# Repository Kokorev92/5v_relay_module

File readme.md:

# Relay module for arduino

A simple relay module for Arduino.

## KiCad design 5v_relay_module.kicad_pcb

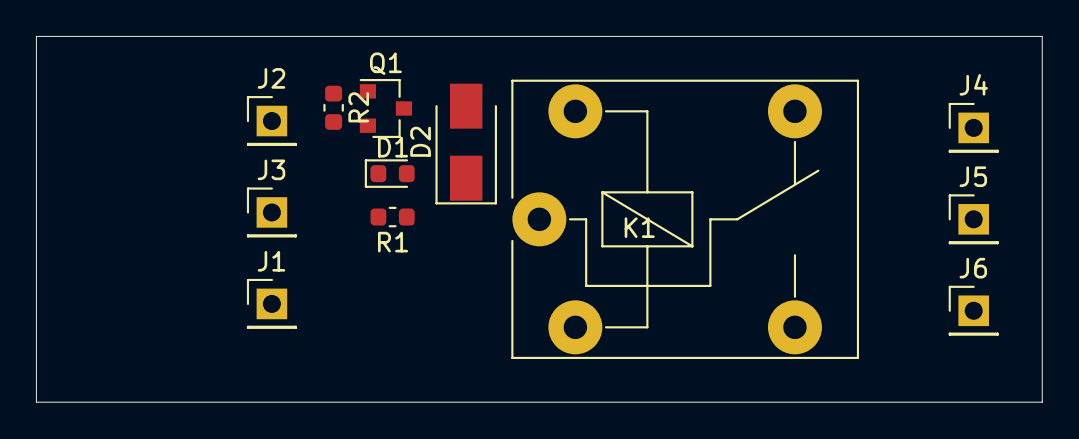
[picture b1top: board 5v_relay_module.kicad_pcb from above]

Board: 2 copper layers, 55.9 x 20.3 mm, 12 parts (0 on the bottom side), 9 nets, no tracks yet.

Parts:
D1: LED; LED_0603_1608Metric
D2: SMA4007; D_SMA
J1, J2, J3, J4, J5, J6: Conn_01x01; PinHeader_1x01_P2.54mm_Vertical
K1: FINDER-34.51.7xxx.x019; Relay_SPDT_Finder_36.11
Q1: BC817; SOT-23
R1: 300; R_0603_1608Metric
R2: 1k; R_0603_1608Metric

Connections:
CNTL: J2.1, R2.2
COM: J5.1, K1.11
GND: J3.1, Q1.2
NC: J4.1, K1.12
NO: J6.1, K1.14
unnamed: D1.1, D2.2, K1.A2, Q1.3
unnamed: D1.2, R1.2
unnamed: Q1.1, R2.1
VIN: D2.1, J1.1, K1.A1, R1.1

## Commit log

2020-03-10 new repository
2020-03-10 add reamde
2021-12-20 [wip]: replacement of components to smd
